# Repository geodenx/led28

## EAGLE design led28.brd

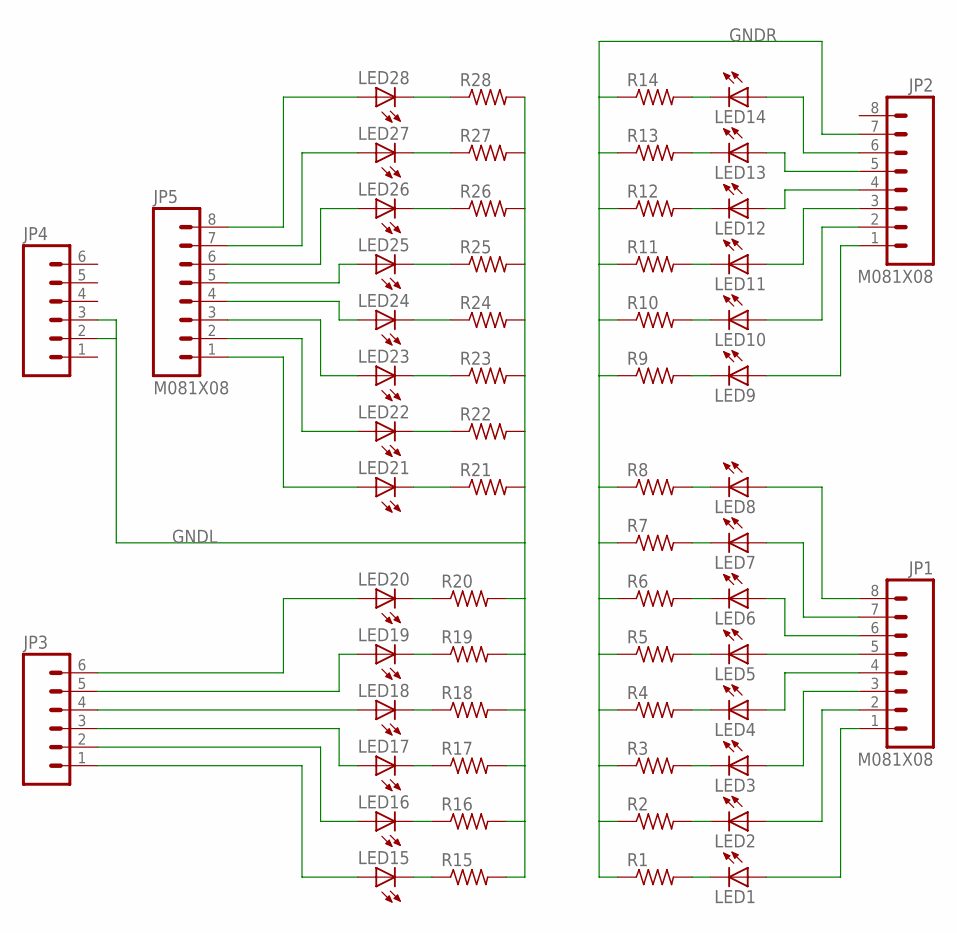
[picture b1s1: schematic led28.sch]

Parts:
JP1, JP2, JP5: M081X08; 1X08_NARROW
JP3, JP4: M06SIP; 1X06_NARROW
LED1, LED2, LED3, LED4, LED5, LED6, LED7, LED8, LED9, LED10, LED11, LED12, LED13, LED14, LED15, LED16, LED17, LED18, LED19, LED20, LED21, LED22, LED23, LED24, LED25, LED26, LED27, LED28: LEDCHIP-LED0603; CHIP-LED0603
R1, R2, R3, R4, R5, R6, R7, R8, R9, R10, R11, R12, R13, R14, R15, R16, R17, R18, R19, R20, R21, R22, R23, R24, R25, R26, R27, R28: R-US_R0603; R0603

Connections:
GNDL: JP4.2, JP4.3, R15.2, R16.2, R17.2, R18.2, R19.2, R20.2, R21.2, R22.2, R23.2, R24.2, R25.2, R26.2, R27.2, R28.2
GNDR: JP2.7, R1.1, R2.1, R3.1, R4.1, R5.1, R6.1, R7.1, R8.1, R9.1, R10.1, R11.1, R12.1, R13.1, R14.1
unnamed: JP1.5, LED5.A
unnamed: JP1.4, LED4.A
unnamed: JP1.3, LED3.A
unnamed: JP1.2, LED2.A
unnamed: JP1.1, LED1.A
unnamed: JP1.6, LED6.A
unnamed: JP1.7, LED7.A
unnamed: JP1.8, LED8.A
unnamed: LED1.C, R1.2
unnamed: LED2.C, R2.2
unnamed: LED3.C, R3.2
unnamed: LED4.C, R4.2
unnamed: LED5.C, R5.2
unnamed: LED6.C, R6.2
unnamed: LED7.C, R7.2
unnamed: LED8.C, R8.2
unnamed: LED9.C, R9.2
unnamed: LED10.C, R10.2
unnamed: LED11.C, R11.2
unnamed: LED12.C, R12.2
unnamed: LED13.C, R13.2
unnamed: LED14.C, R14.2
unnamed: JP2.4, LED12.A
unnamed: JP2.3, LED11.A
unnamed: JP2.2, LED10.A
unnamed: JP2.1, LED9.A
unnamed: JP2.5, LED13.A
unnamed: JP2.6, LED14.A
unnamed: LED15.C, R15.1
unnamed: LED16.C, R16.1
unnamed: LED17.C, R17.1
unnamed: LED18.C, R18.1
unnamed: LED19.C, R19.1
unnamed: LED20.C, R20.1
unnamed: LED21.C, R21.1
unnamed: LED22.C, R22.1
unnamed: LED23.C, R23.1
unnamed: LED24.C, R24.1
unnamed: LED25.C, R25.1
unnamed: LED26.C, R26.1
unnamed: LED27.C, R27.1
unnamed: LED28.C, R28.1
unnamed: JP3.4, LED18.A
unnamed: JP3.3, LED17.A
unnamed: JP3.2, LED16.A
unnamed: JP3.1, LED15.A
unnamed: JP5.4, LED24.A
unnamed: JP5.3, LED23.A
unnamed: JP5.2, LED22.A
unnamed: JP5.1, LED21.A
unnamed: JP5.5, LED25.A
unnamed: JP5.6, LED26.A
unnamed: JP5.7, LED27.A
unnamed: JP5.8, LED28.A
unnamed: JP3.5, LED19.A
unnamed: JP3.6, LED20.A

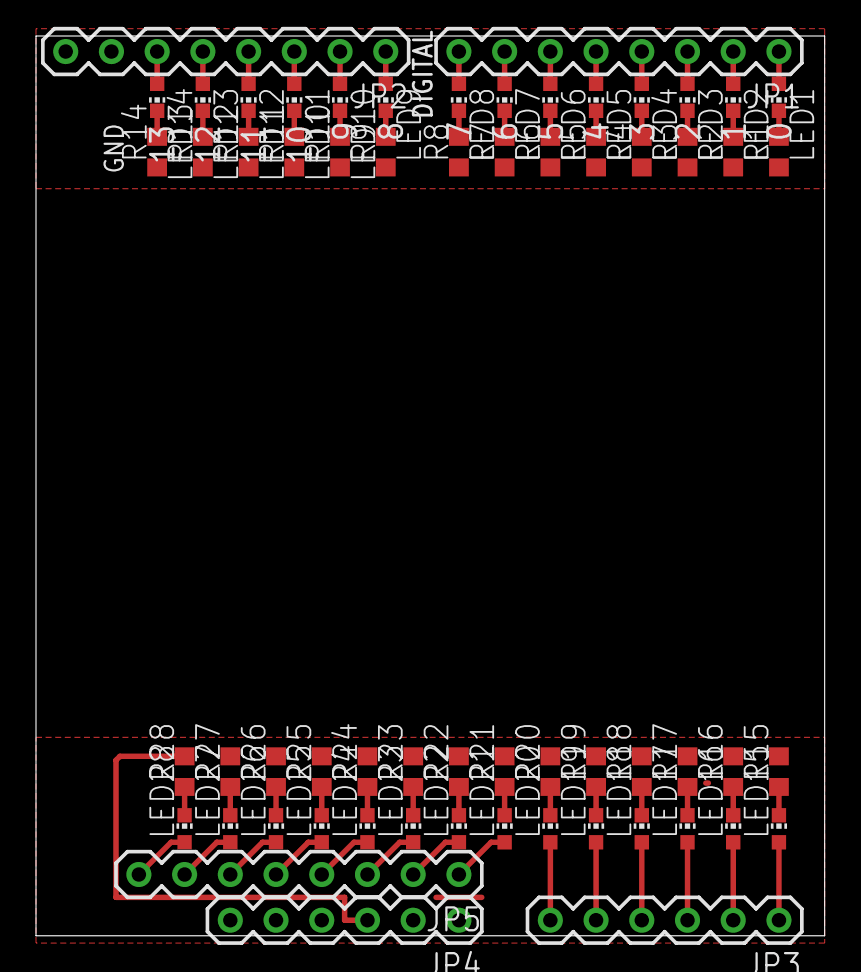
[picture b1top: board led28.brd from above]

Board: 2 copper layers, 43.8 x 50.0 mm, 61 parts (0 on the bottom side), 58 nets.

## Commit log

2012-07-30 Added led28.sch led28.brd
2012-07-31 Added gerber and PDF
2012-07-31 Fit dimension in 50mm
2012-08-01 Fix rand (round 55mil, 0.8mm drill)
2012-08-01 Moved silk and fixed GND pattern
2012-08-01 As of ordering
2012-08-01 Added led28.lbr
2012-08-01 Added a special CAM processor wo/generating top silk
2012-08-02 Removed universal area
